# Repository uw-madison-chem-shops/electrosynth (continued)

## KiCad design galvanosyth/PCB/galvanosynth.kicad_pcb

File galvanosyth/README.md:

# galvanosynth

An inexpensive circuit made for driving multiple electrochemical constant current reactions.

Each galvanosynth is made of three custom components:

- the main driver PCB
- the front panel PCB
- 3D printed bracket

See subdirectories for detailed instructions on each of these components.

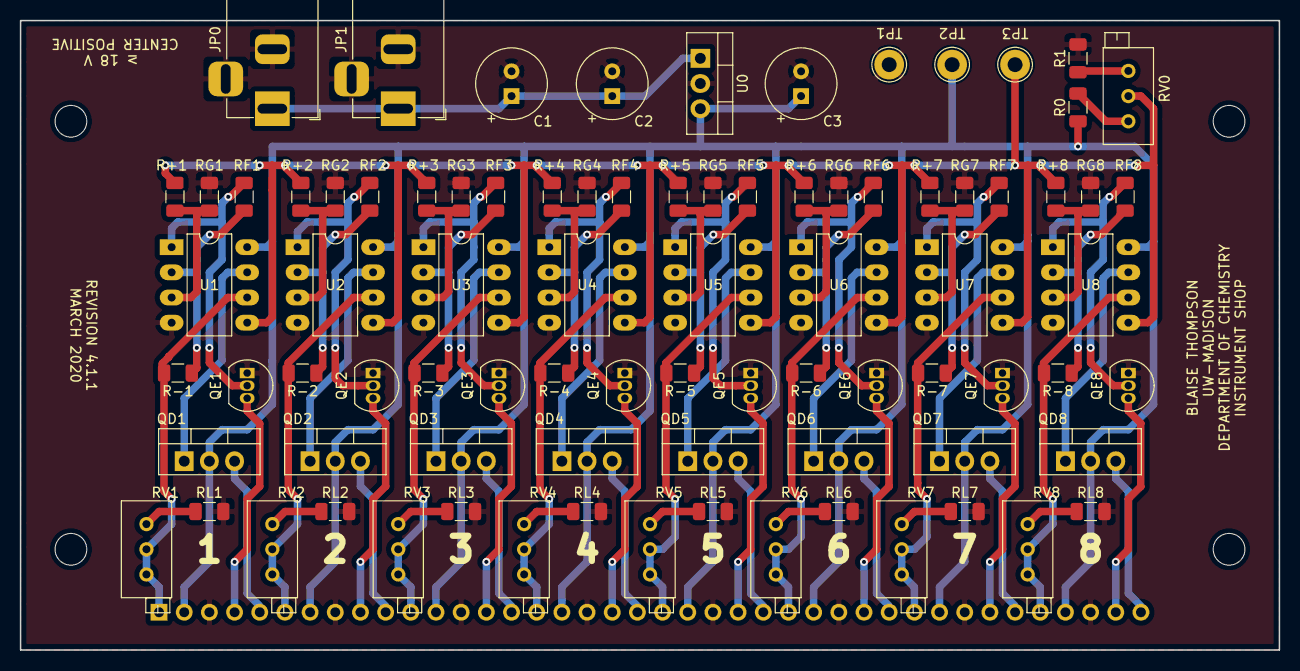
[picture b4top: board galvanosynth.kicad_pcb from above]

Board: 2 copper layers, 127.0 x 63.5 mm, 85 parts (1 on the bottom side), 70 nets.

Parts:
C1: 100uF; CP_Radial_Tantal_D7.0mm_P2.50mm
C2: 330nF; CP_Radial_Tantal_D7.0mm_P2.50mm
C3: 100nF; CP_Radial_Tantal_D7.0mm_P2.50mm
J1: Conn_01x40; PinHeader_1x40_P2.54mm_Horizontal
JP0, JP1: Barrel_Jack_Switch; BarrelJack_Horizontal
QD1, QD2, QD3, QD4, QD5, QD6, QD7, QD8: IRF630; TO-220-3_Vertical
QE1, QE2, QE3, QE4, QE5, QE6, QE7, QE8: 2N7000; TO-92_Inline
R0: 10k; R_1206_3216Metric
R1: 68; R_1206_3216Metric
R+1, R+2, R+3, R+4, R+5, R+6, R+7, R+8: 1k; R_1206_3216Metric
R-1, R-2, R-3, R-4, R-5, R-6, R-7, R-8: 1k; R_1206_3216Metric
RF1, RF2, RF3, RF4, RF5, RF6, RF7, RF8: 100k; R_1206_3216Metric
RG1, RG2, RG3, RG4, RG5, RG6, RG7, RG8: 100k; R_1206_3216Metric
RL1, RL2, RL3, RL4, RL5, RL6, RL7, RL8: 10; R_1206_3216Metric
RV0: 1k; Potentiometer_Bourns_3296X_Horizontal
RV1, RV2, RV3, RV4, RV5, RV6, RV7, RV8: 2k; Potentiometer_Bourns_3296X_Horizontal
TP1, TP2, TP3: TestPoint; TestPoint_THTPad_D3.0mm_Drill1.5mm
U0: L7815; TO-220-3_Vertical
U1, U2, U3, U4, U5, U6, U7, U8: LM358; DIP-8_W7.62mm_LongPads

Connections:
+15V: C3.1, J1.2, J1.7, J1.12, J1.17, J1.22, J1.27, J1.32, J1.37, QD1.2, QD2.2, QD3.2, QD4.2, QD5.2, QD6.2, QD7.2, QD8.2, R0.1, TP2.1, U0.3, U1.8, U2.8, U3.8, U4.8, U5.8, U6.8, U7.8, U8.8
/1/CONTROL: R+1.1, R+2.1, R+3.1, R+4.1, R+5.1, R+6.1, R+7.1, R+8.1, RV0.2, TP3.1, U1.5, U2.5, U3.5, U4.5, U5.5, U6.5, U7.5, U8.5
/1/ERROR: J1.4, QE1.3
/1/RETURN: J1.1, R-1.2, RV1.2, RV1.3, U1.6
/1/SUPPLY: J1.5, QD1.3
/2/ERROR: J1.9, QE2.3
/2/RETURN: J1.6, R-2.2, RV2.2, RV2.3, U2.6
/2/SUPPLY: J1.10, QD2.3
/3/ERROR: J1.14, QE3.3
/3/RETURN: J1.11, R-3.2, RV3.2, RV3.3, U3.6
/3/SUPPLY: J1.15, QD3.3
/4/ERROR: J1.19, QE4.3
/4/RETURN: J1.16, R-4.2, RV4.2, RV4.3, U4.6
/4/SUPPLY: J1.20, QD4.3
/5/ERROR: J1.24, QE5.3
/5/RETURN: J1.21, R-5.2, RV5.2, RV5.3, U5.6
/5/SUPPLY: J1.25, QD5.3
/6/ERROR: J1.29, QE6.3
/6/RETURN: J1.26, R-6.2, RV6.2, RV6.3, U6.6
/6/SUPPLY: J1.30, QD6.3
/7/ERROR: J1.34, QE7.3
/7/RETURN: J1.31, R-7.2, RV7.2, RV7.3, U7.6
/7/SUPPLY: J1.35, QD7.3
/8/ERROR: J1.39, QE8.3
/8/RETURN: J1.36, R-8.2, RV8.2, RV8.3, U8.6
/8/SUPPLY: J1.40, QD8.3
GND: C1.2, C2.2, C3.2, J1.3, J1.8, J1.13, J1.18, J1.23, J1.28, J1.33, J1.38, JP0.2, JP0.3, JP1.2, JP1.3, QE1.1, QE2.1, QE3.1, QE4.1, QE5.1, QE6.1, QE7.1, QE8.1, R1.2, RG1.2, RG2.2, RG3.2, RG4.2, RG5.2, RG6.2, RG7.2, RG8.2, RL1.1, RL2.1, RL3.1, RL4.1, RL5.1, RL6.1, RL7.1, RL8.1, TP1.1, U0.2, U1.4, U2.4, U3.4, U4.4, U5.4, U6.4, U7.4, U8.4
unnamed: C1.1, C2.1, JP0.1, JP1.1, U0.1
unnamed: QD1.1, U1.7
unnamed: QD2.1, U2.7
unnamed: QD3.1, U3.7
unnamed: QD4.1, U4.7
unnamed: QD5.1, U5.7
unnamed: QD6.1, U6.7
unnamed: QD7.1, U7.7
unnamed: QD8.1, U8.7
unnamed: QE1.2, RF1.2, U1.1
unnamed: QE2.2, RF2.2, U2.1
unnamed: QE3.2, RF3.2, U3.1
unnamed: QE4.2, RF4.2, U4.1
unnamed: QE5.2, RF5.2, U5.1
unnamed: QE6.2, RF6.2, U6.1
unnamed: QE7.2, RF7.2, U7.1
unnamed: QE8.2, RF8.2, U8.1
unnamed: R0.2, RV0.1
unnamed: R1.1, RV0.3
unnamed: R+1.2, RG1.1, U1.3
unnamed: R+2.2, RG2.1, U2.3
unnamed: R+3.2, RG3.1, U3.3
unnamed: R+4.2, RG4.1, U4.3
unnamed: R+5.2, RG5.1, U5.3
unnamed: R+6.2, RG6.1, U6.3
unnamed: R+7.2, RG7.1, U7.3
unnamed: R+8.2, RG8.1, U8.3
unnamed: R-1.1, RF1.1, U1.2
unnamed: R-2.1, RF2.1, U2.2
unnamed: R-3.1, RF3.1, U3.2
unnamed: R-4.1, RF4.1, U4.2
unnamed: R-5.1, RF5.1, U5.2
unnamed: R-6.1, RF6.1, U6.2
unnamed: R-7.1, RF7.1, U7.2
unnamed: R-8.1, RF8.1, U8.2
unnamed: RL1.2, RV1.1
unnamed: RL2.2, RV2.1
unnamed: RL3.2, RV3.1
unnamed: RL4.2, RV4.1
unnamed: RL5.2, RV5.1
unnamed: RL6.2, RV6.1
unnamed: RL7.2, RV7.1
unnamed: RL8.2, RV8.1

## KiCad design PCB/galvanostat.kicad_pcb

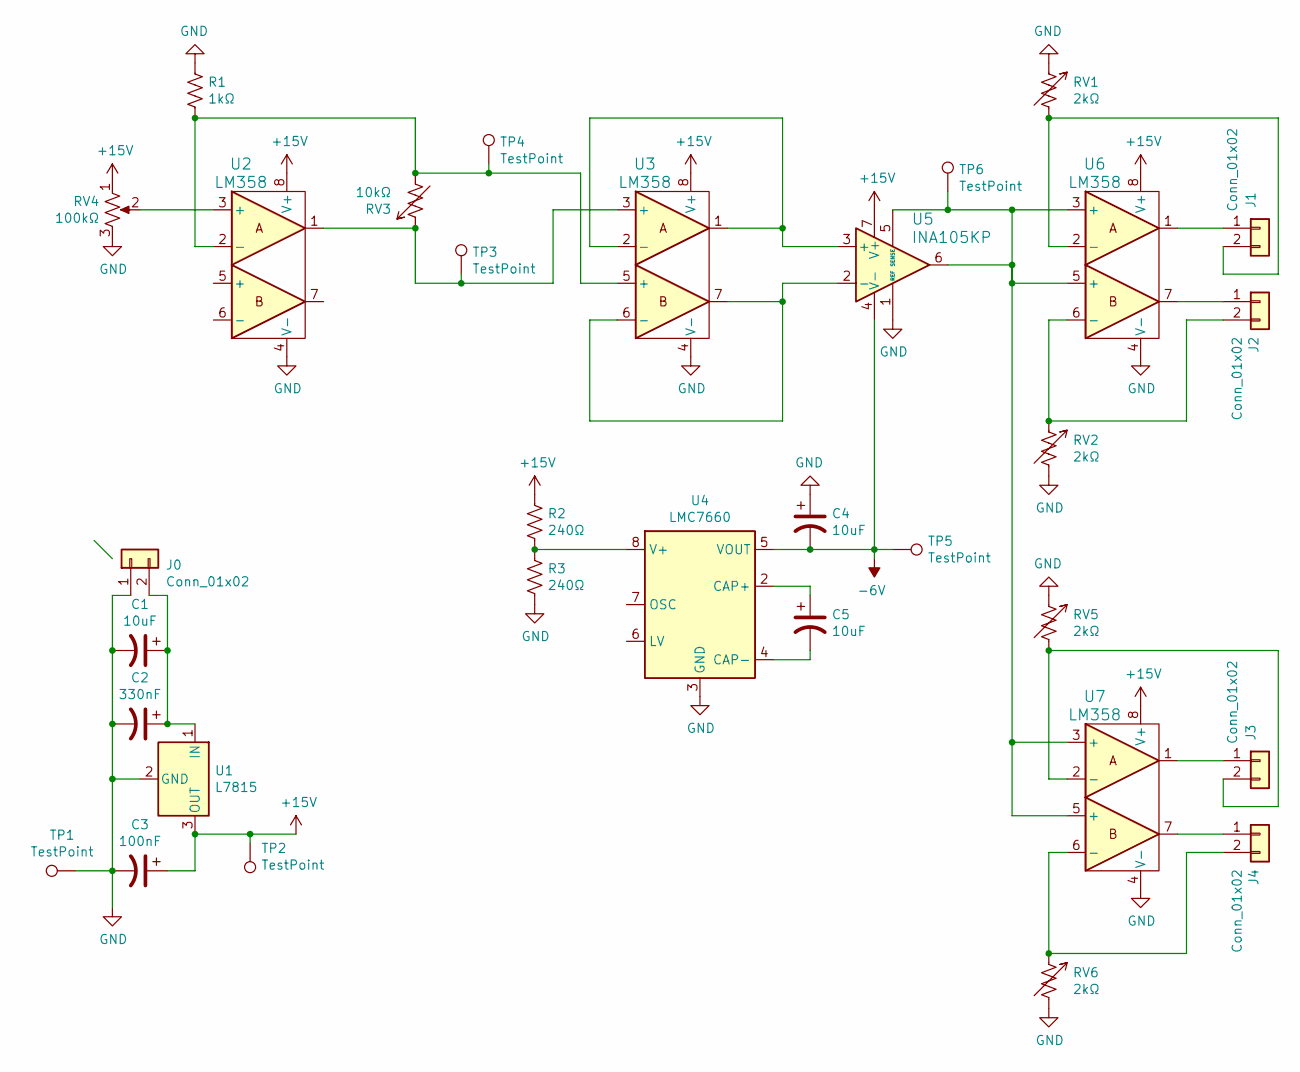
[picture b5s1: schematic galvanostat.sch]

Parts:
C1, C4, C5: 10uF; CP_Radial_Tantal_D7.0mm_P2.50mm
C2: 330nF; CP_Radial_Tantal_D7.0mm_P2.50mm
C3: 100nF; CP_Radial_Tantal_D7.0mm_P2.50mm
J0, J1, J2, J3, J4: Conn_01x02; Molex_KK-254_AE-6410-02A_1x02_P2.54mm_Vertical
R1: 1kΩ; R_Axial_DIN0207_L6.3mm_D2.5mm_P10.16mm_Horizontal
R2, R3: 240Ω; R_Axial_DIN0207_L6.3mm_D2.5mm_P10.16mm_Horizontal
RV1, RV2, RV5, RV6: 2kΩ; Potentiometer_Bourns_3299W_Vertical
RV3: 10kΩ; Molex_KK-254_AE-6410-02A_1x02_P2.54mm_Vertical
RV4: 100kΩ; Potentiometer_Bourns_3299W_Vertical
TP1, TP2, TP3, TP4, TP5, TP6: TestPoint; TestPoint_THTPad_D3.0mm_Drill1.5mm
U1: L7815; TO-220-3_Vertical
U2, U3, U6, U7: LM358; DIP-8_W7.62mm_Socket_LongPads
U4: LMC7660; DIP-8_W7.62mm_Socket_LongPads
U5: INA105KP; DIP-8_W7.62mm_Socket_LongPads

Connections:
+15V: C3.1, R2.2, RV4.1, TP2.1, U1.3 (OUT), U2.8 (V+), U3.8 (V+), U5.7 (V+), U6.8 (V+), U7.8 (V+)
-6V: C4.2, TP5.1, U4.5 (VOUT), U5.4 (V-)
GND: C1.2, C2.2, C3.2, C4.1, J0.1, R1.1, R3.2, RV1.1, RV2.2, RV4.3, RV5.1, RV6.2, TP1.1, U1.2 (GND), U2.4 (V-), U3.4 (V-), U4.3 (GND), U5.1 (REF), U6.4 (V-), U7.4 (V-)
unnamed: C1.1, C2.1, J0.2, U1.1 (IN)
unnamed: C5.1, U4.2 (CAP+)
unnamed: C5.2, U4.4 (CAP-)
unnamed: J1.1, U6.1
unnamed: J1.2, RV1.2, U6.2 (-)
unnamed: J2.1, U6.7
unnamed: J2.2, RV2.1, U6.6 (-)
unnamed: J3.1, U7.1
unnamed: J3.2, RV5.2, U7.2 (-)
unnamed: J4.1, U7.7
unnamed: J4.2, RV6.1, U7.6 (-)
unnamed: R1.2, RV3.2, TP4.1, U2.2 (-), U3.5 (+)
unnamed: R2.1, R3.1, U4.8 (V+)
unnamed: RV3.1, TP3.1, U2.1, U3.3 (+)
unnamed: RV4.2, U2.3 (+)
unnamed: TP6.1, U5.5 (SENSE), U5.6, U6.3 (+), U6.5 (+), U7.3 (+), U7.5 (+)
unnamed: U3.1, U3.2 (-), U5.3 (+)
unnamed: U3.6 (-), U3.7, U5.2 (-)

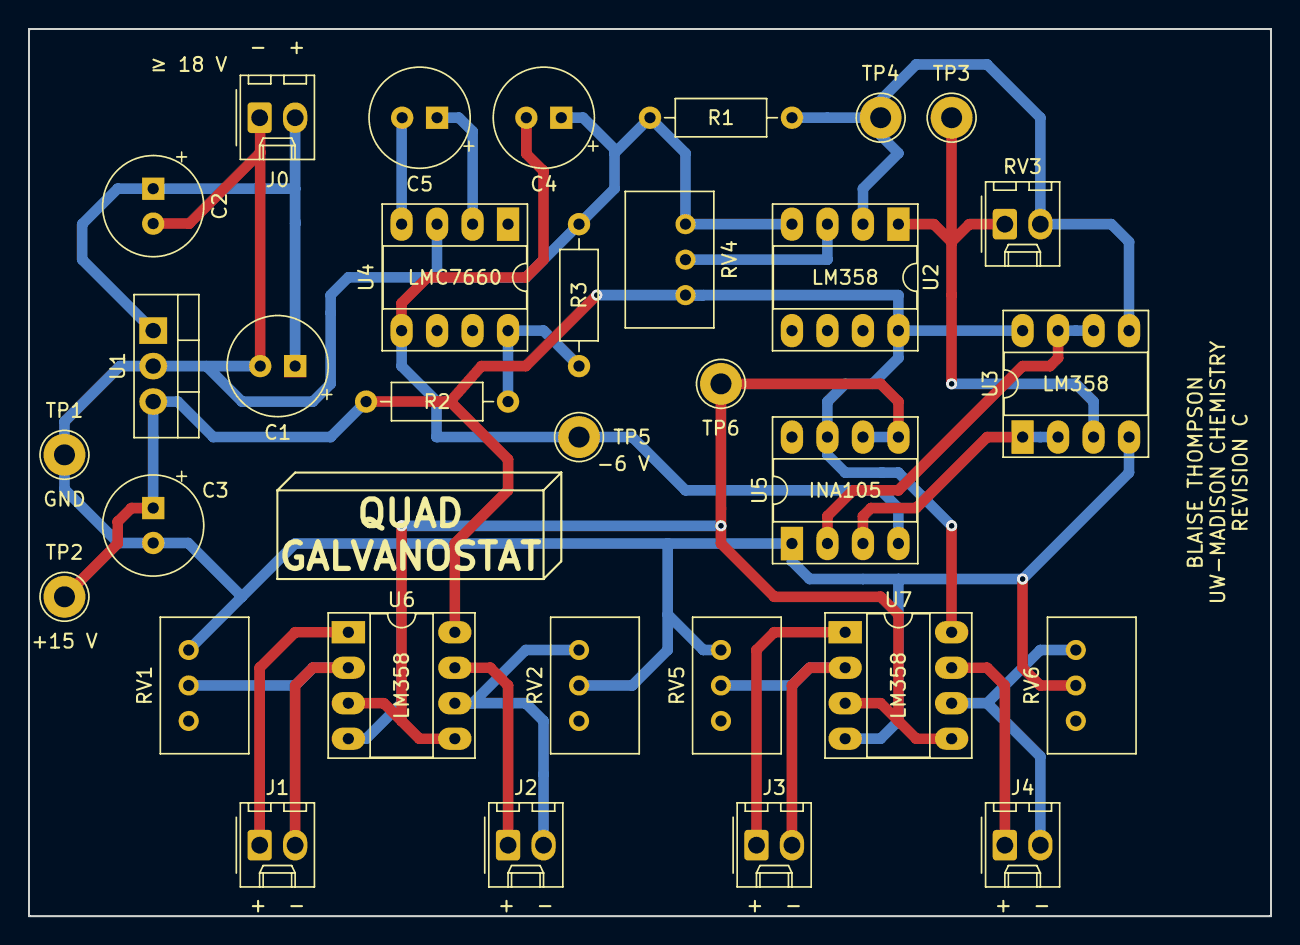
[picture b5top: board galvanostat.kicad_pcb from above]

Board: 2 copper layers, 88.9 x 63.5 mm, 32 parts (0 on the bottom side), 21 nets.

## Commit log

2018-11-14 2018-11-13 19:01
2018-11-14 2018-11-14 12:00
2018-11-14 2018-11-14 13:05
2019-06-11 dual to quad
2019-06-25 revision C
2020-01-29 4.0.0
2020-01-29 daughter
2020-08-11 forgotten
2021-04-06 organize
2021-04-06 license
2021-05-05 reorg potentiosynth
2021-05-07 restructure galvanosynth
2021-05-07 galvo front panel organize
2021-05-07 coverart
2021-05-07 prepare for potentiosynth
2021-05-07 first draft driver-pcb
2021-05-07 first draft front panel
2021-07-07 added buffer amplifier
2021-07-07 fixed potentiosynth front panel silkscreen
2021-07-07 forgotten fills
2021-07-09 add fuse
2021-07-09 potentiosynth-front-panel-revB
2021-08-04 revB
2021-08-04 remotes
2021-10-08 resistor net
2021-10-12 potentiosynth driver revC
2021-11-05 uncommitted changes
2023-07-17 Bills of Materials Update
2023-07-17 Update Bill of Materials
2023-07-18 Added amount per board column
2023-08-07 Bills of Materials Updated (#9)
    * Bills of Materials Update
    * Update README.md
    * Update README.md
    * Update Bill of Materials
    * Update README.md
    * Update README.md
